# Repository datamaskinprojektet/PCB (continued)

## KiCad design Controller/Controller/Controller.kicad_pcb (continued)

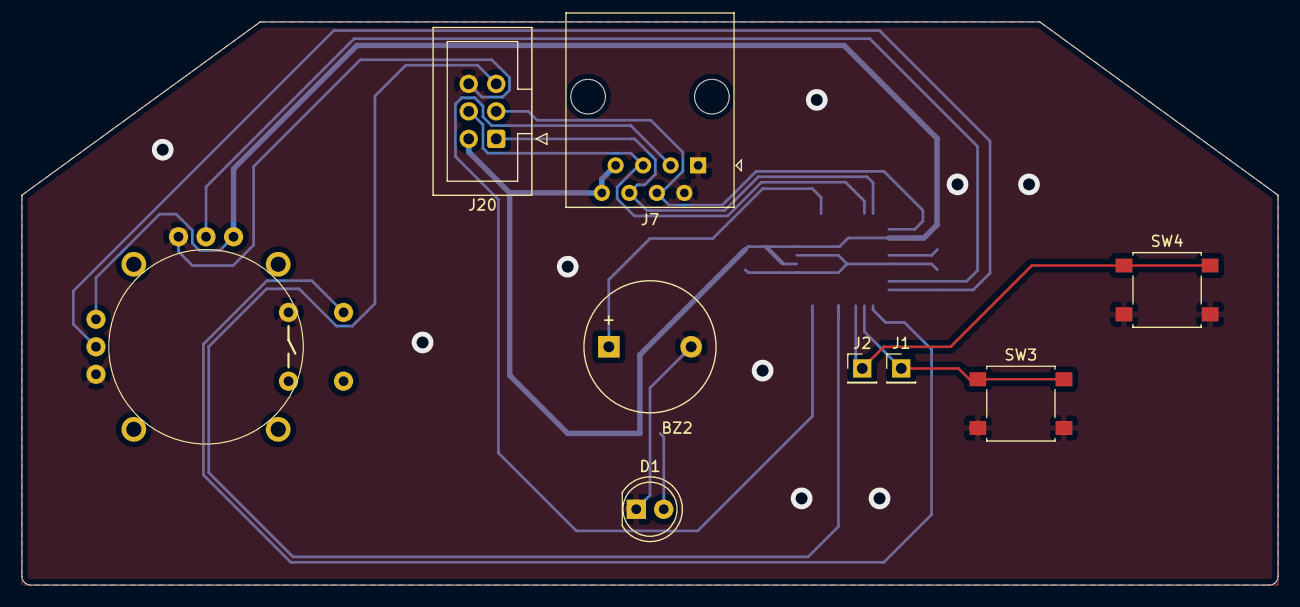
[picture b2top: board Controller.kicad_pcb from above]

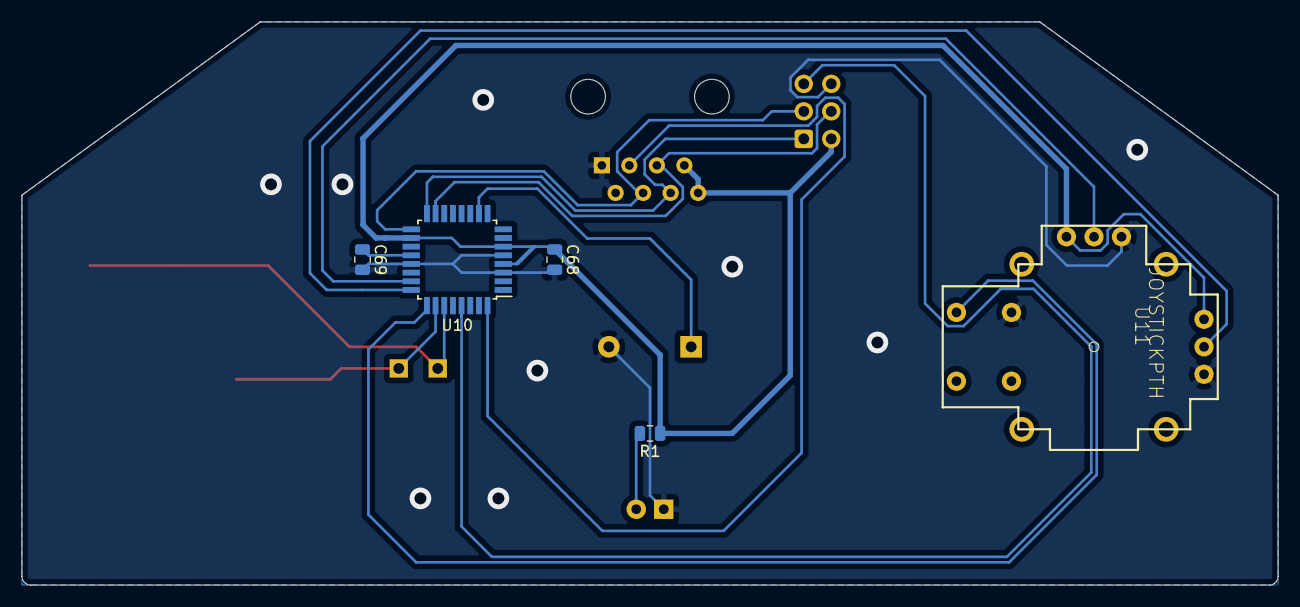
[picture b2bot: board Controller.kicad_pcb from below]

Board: 2 copper layers, 116.0 x 52.0 mm, 13 parts (4 on the bottom side), 15 nets.

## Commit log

2020-09-02 Added some mcu datasheets
2020-09-02 Added ignore files
2020-09-02 Added fpga datasheets
2020-09-09 Add kicad git sugar
2020-09-13 Add README alongside creating project
2020-09-15 Add SMPS schematic
2020-09-16 Made schematic not have a date
2020-09-17 Added FPGA implimentation without OSC
2020-09-18 Added EFM32 Giant Gecko (lib and sch)
2020-09-18 Fix bak-files not being ignored
2020-09-18 Created schematic symbol for SRAM
2020-09-20 Added power circuitry to EFM32
2020-09-20 Added separation lines and title. Removed orphaned 3.3v node in the middle of nowhere
2020-09-20 Rescued RAM module lib
2020-09-20 Dunno what happened last commit but I need to commit again
2020-09-20 Added HDMI
2020-09-20 gits
2020-09-20 Fixed .gitignore. Added erc reports to .gitignore
2020-09-21 Added power flags to power nodes
2020-09-21 Made capacitors on MCU power prettier
2020-09-21 Added PWR_FLAG to 3v3
2020-09-21 Changed EFM to use 3.3VA instead of filtering its own power
2020-09-21 Added HDMI and VGA support
2020-09-21 Assigned footprints and Started PCB layout
2020-09-24 Added usb + minor fixes
2020-09-24 Added library for joystick m.m
2020-09-24 Added multiplex option on SD-card and onboard controller
2020-09-25 Fixed minor mistakes and worked on PCB layout
2020-09-28 New EFM model and PCB layout in progress
2020-09-28 Rescued symbol libraries
2020-09-28 Good progress on routing
2020-09-29 Finished most tracing and changed some bus pins
2020-09-29 Progress in layout
2020-09-29 Gir meg for kvelden
2020-09-29 Added symbol lib for custom LDOs
2020-09-30 Added LDOs to schema
2020-09-30 Annotated schematic
2020-09-30 Added capacitors to 5V LDO
2020-09-30 Changed MAX8869 LDO to use footprint with EP
2020-09-30 Changed LDO sheet to not use the TI LDO since it has ~EN instead od ~SHDN for some reason. Unusable without an inverter, which I don't feel like making
2020-09-30 Wired up the LDOs in eeschema
2020-09-30 Added output caps to 1.0, 1.8 and 3.3 volt LDOs
2020-09-30 Changed µF to u
2020-09-30 Complete Schematic
2020-09-30 Fixed ERC errors due to MAX8869 having multiple 'power output' pins
2020-09-30 Moved power supply labels to make it more obvious what they label
2020-09-30 Routed all unused IO pins on the FPGA to headers
2020-09-30 marked SW1 on U1 as not connected
2020-09-30 Added NC flag to HDMI utility pin
2020-09-30 Added power status LEDs to 5V and 3V3
2020-09-30 Finished essensial routing
2020-09-30 Fixes one track
2020-09-30 marked some pins on VGA connector as NC
2020-09-30 Added headers to audio MCU. Added 9v barrel jack as power supply connector
2020-09-30 all unused pins are now connected
2020-09-30 Fixed visual bug where it looked like EBI_AD nad EBI_CS was mixed up on the FPGA
2020-10-01 Ready for ordering
2020-10-01 Fixed graphics
2020-10-01 Fixed mistake
2020-10-05 Version 2 for production
2020-10-05 Fixed via sizes
2020-10-05 Fixed another set of via sizes
2020-11-05 Added KiCAD projects for various extra parts, added different 3d models and a vivado hardware test project
2020-11-24 Added FPGA test code and 3d files for printing
2020-11-24 Started conversion of PCB to smaller card, removed some redundancy
2020-11-26 Added new footprints and components
2020-11-26 Started routing for FPGA
